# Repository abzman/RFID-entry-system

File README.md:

RFID-entry-system
=================

RFID entry system for i3 Detroit based on the Open Access Control 3.0, ethernet shield v5, arduino mega 2560, and Static Controls Corporation 1080 displays (RS485)

For an up to date overview please visit http://i3detroit.com/wi/index.php?title=RFID_entry_system

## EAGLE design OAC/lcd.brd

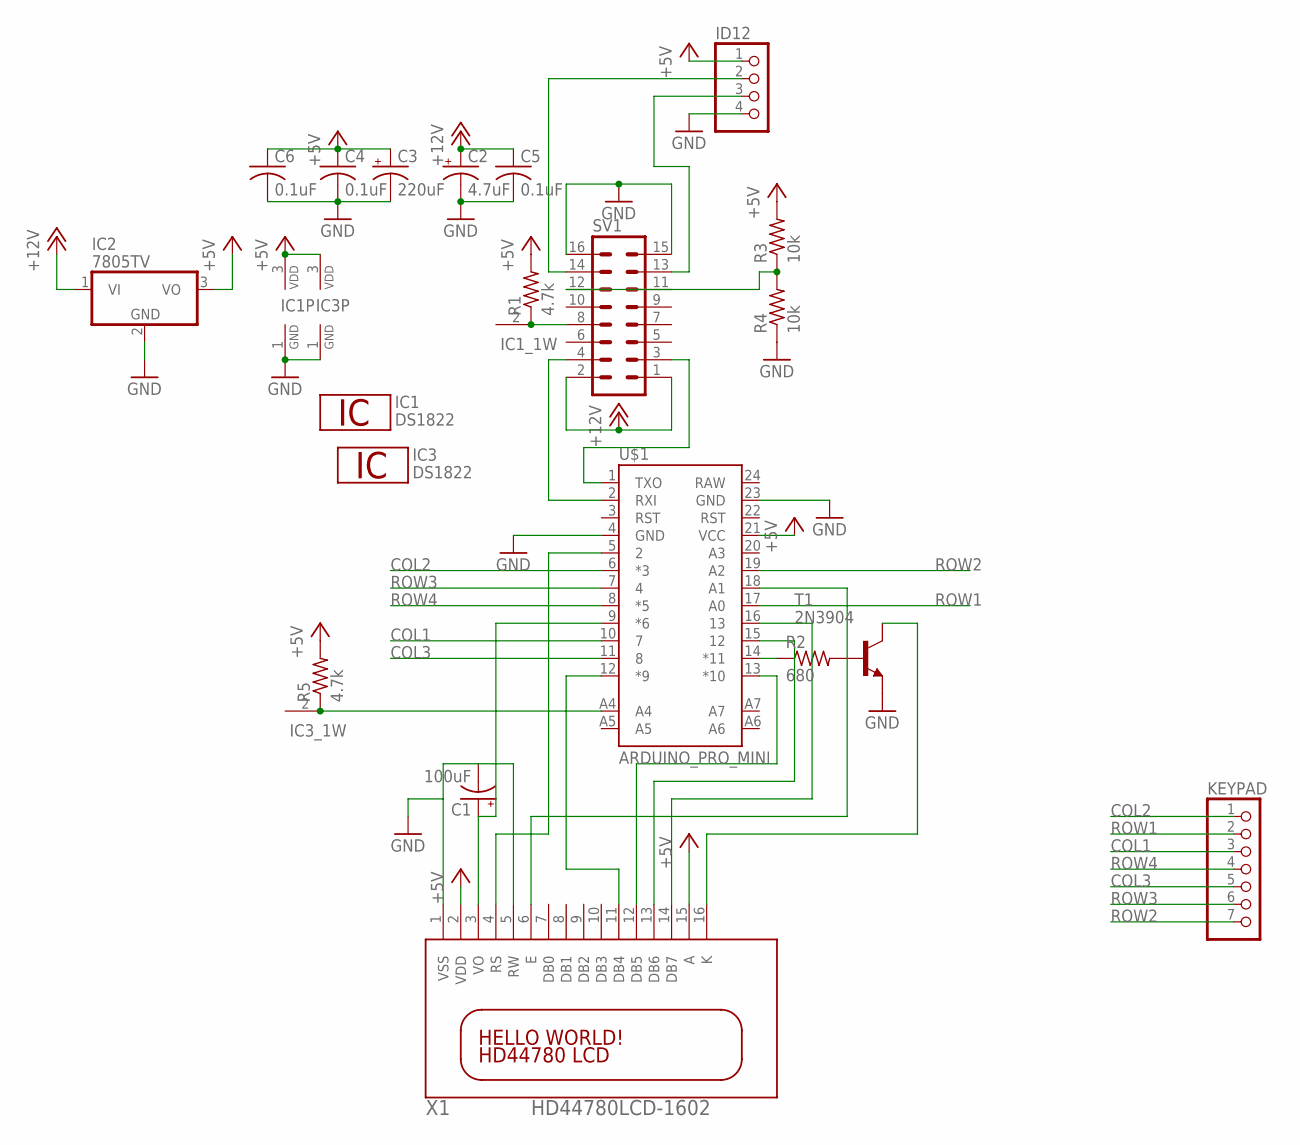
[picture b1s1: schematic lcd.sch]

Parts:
C1: 100uF; E2,5-7
C2: 4.7uF; E2,5-6
C3: 220uF; E5-8,5
C4, C5, C6: 0.1uF; C025-025X050
IC1, IC3: DS1822; TO92-
IC2: 7805TV; TO220V
ID12: PINHD-1X4; 1X04
KEYPAD: PINHD-1X7; 1X07
R1, R5: 4.7k; 0207/5V
R2: 680; 0207/5V
R3, R4: 10k; 0204V
SV1: ML16
T1: 2N3904; TO92
U$1: ARDUINO_PRO_MINI
X1: HD44780LCD-1602; LCD1602

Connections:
+5V: C3.+, C4.1, C6.1, IC1.3 (VDD), IC2.3 (VO), IC3.3 (VDD), ID12.1, R1.2, R3.2, R5.2, U$1.21 (VCC), X1.2 (VDD), X1.15 (A)
+12V: C2.+, C5.1, IC2.1 (VI), SV1.1, SV1.2
COL1: KEYPAD.3, U$1.10 (7)
COL2: KEYPAD.1, U$1.6 (*3)
COL3: KEYPAD.5, U$1.11 (8)
GND: C1.-, C2.-, C3.-, C4.2, C5.2, C6.2, IC1.1 (GND), IC2.2 (GND), IC3.1 (GND), ID12.4, R4.1, SV1.15, SV1.16, T1.3 (E), U$1.4 (GND), U$1.23 (GND), X1.1 (VSS), X1.5 (RW)
unnamed: IC1.2 (1W), R1.1, SV1.8
unnamed: C1.+, U$1.9 (*6), X1.3 (VO)
unnamed: SV1.4, U$1.2 (RXI)
unnamed: R2.1, U$1.14 (*11)
unnamed: R2.2, T1.2 (B)
unnamed: SV1.3, U$1.1 (TXO)
unnamed: ID12.2, SV1.14
unnamed: ID12.3, SV1.13
unnamed: T1.1 (C), X1.16 (K)
unnamed: U$1.5 (2), X1.4 (RS)
unnamed: U$1.18 (A1), X1.6 (E)
unnamed: U$1.12 (*9), X1.11 (DB4)
unnamed: U$1.13 (*10), X1.12 (DB5)
unnamed: U$1.15 (12), X1.13 (DB6)
unnamed: U$1.16 (13), X1.14 (DB7)
unnamed: R3.1, R4.2, SV1.12
unnamed: IC3.2 (1W), R5.1, U$1.A4
ROW1: KEYPAD.2, U$1.17 (A0)
ROW2: KEYPAD.7, U$1.19 (A2)
ROW3: KEYPAD.6, U$1.7 (4)
ROW4: KEYPAD.4, U$1.8 (*5)

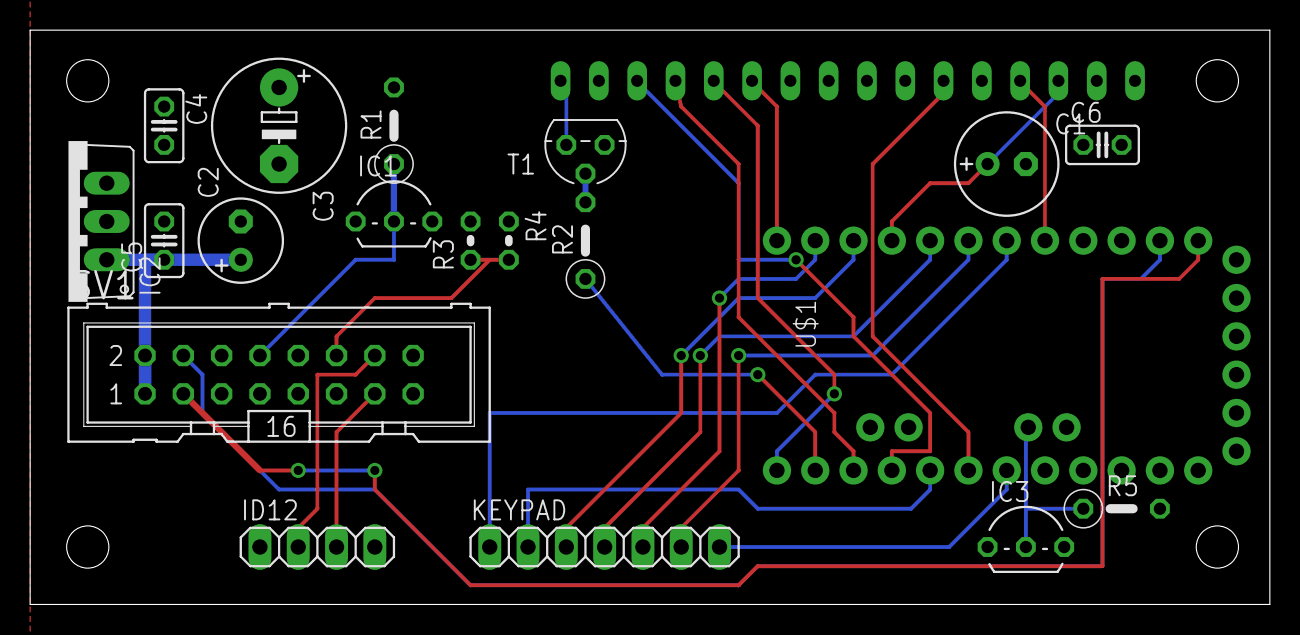
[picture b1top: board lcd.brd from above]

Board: 2 copper layers, 82.2 x 38.1 mm, 20 parts (1 on the bottom side), 27 nets.

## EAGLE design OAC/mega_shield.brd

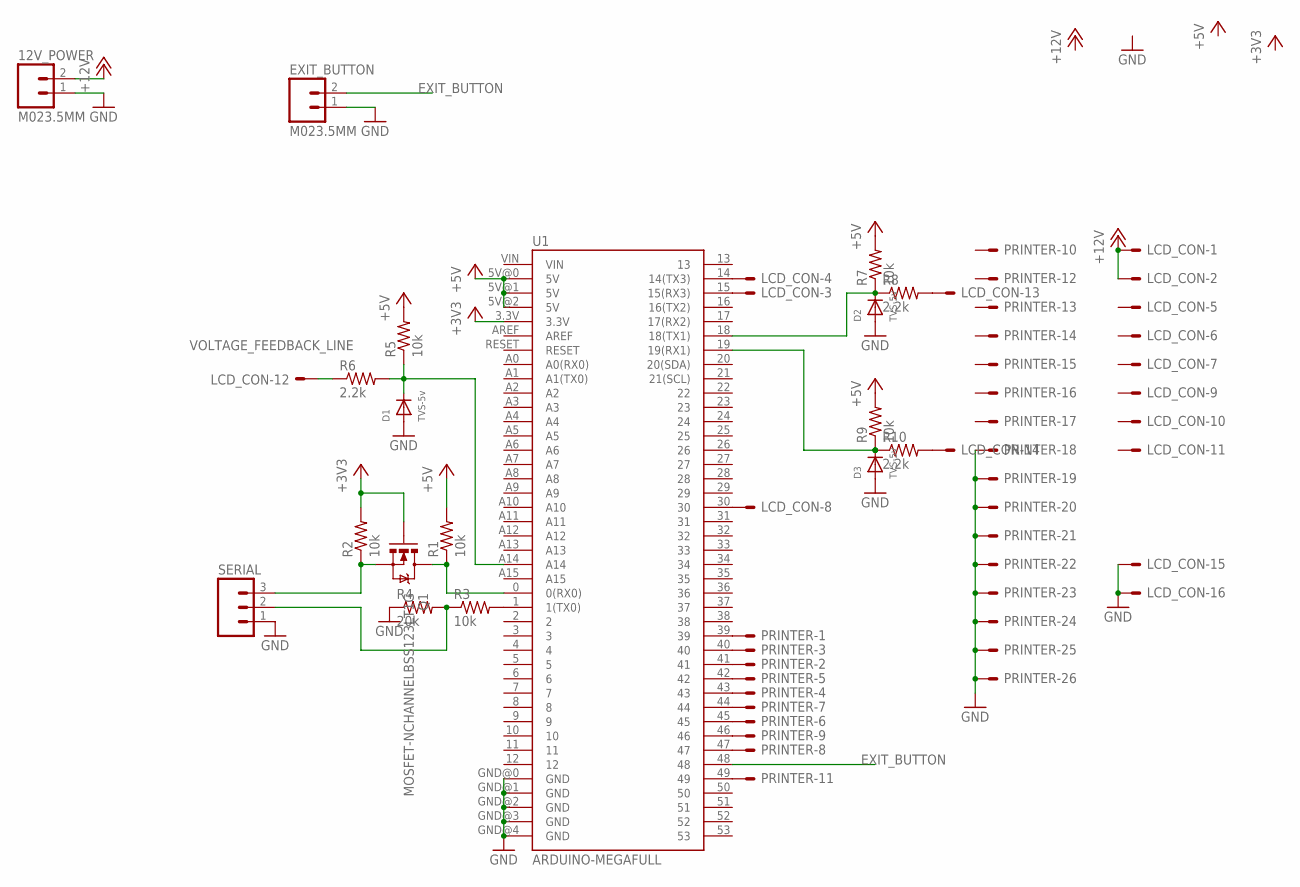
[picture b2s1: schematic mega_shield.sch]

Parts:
12V_POWER: M023.5MM; SCREWTERMINAL-3.5MM-2
D1, D2, D3: TVS-5v; SOD-123
EXIT_BUTTON: M023.5MM; SCREWTERMINAL-3.5MM-2
LCD_CON: ML16E; ML16
PRINTER: ML26E; ML26
Q1: MOSFET-NCHANNELBSS123LT1G; SOT23
R1, R2, R3, R5, R7, R9: 10k; R0603
R4: 20k; R0603
R6, R8, R10: 2.2k; R0603
SERIAL: M03SCREW; SCREWTERMINAL-3.5MM-3
U1: ARDUINO-MEGAFULL; ARDUINO_MEGA

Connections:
+3V3: Q1.1 (G), R2.2, U1.3.3V
+5V: R1.2, R5.2, R7.2, R9.2, U1.5V@0 (5V), U1.5V@1 (5V), U1.5V@2 (5V)
+12V: 12V_POWER.2, LCD_CON.1, LCD_CON.2
EXIT_BUTTON: EXIT_BUTTON.2, U1.48
GND: 12V_POWER.1, D1.A, D2.A, D3.A, EXIT_BUTTON.1, LCD_CON.15, LCD_CON.16, PRINTER.18, PRINTER.19, PRINTER.20, PRINTER.21, PRINTER.22, PRINTER.23, PRINTER.24, PRINTER.25, PRINTER.26, R4.1, SERIAL.1, U1.GND@0 (GND), U1.GND@1 (GND), U1.GND@2 (GND), U1.GND@3 (GND), U1.GND@4 (GND)
unnamed: LCD_CON.3, U1.15 (15(RX3))
unnamed: LCD_CON.4, U1.14 (14(TX3))
unnamed: PRINTER.1, U1.39
unnamed: PRINTER.11, U1.49
unnamed: PRINTER.2, U1.41
unnamed: PRINTER.3, U1.40
unnamed: PRINTER.4, U1.43
unnamed: PRINTER.5, U1.42
unnamed: PRINTER.6, U1.45
unnamed: PRINTER.7, U1.44
unnamed: PRINTER.8, U1.47
unnamed: PRINTER.9, U1.46
unnamed: LCD_CON.8, U1.30
unnamed: R3.2, U1.1 (1(TX0))
unnamed: R3.1, R4.2, SERIAL.2
unnamed: D1.C, R5.1, R6.2, U1.A14
unnamed: Q1.2 (S), R2.1, SERIAL.3
unnamed: Q1.3 (D), R1.1, U1.0 (0(RX0))
unnamed: D2.C, R7.1, R8.1, U1.18 (18(TX1))
unnamed: D3.C, R9.1, R10.1, U1.19 (19(RX1))
unnamed: LCD_CON.13, R8.2
unnamed: LCD_CON.14, R10.2
VOLTAGE_FEEDBACK_LINE: LCD_CON.12, R6.1

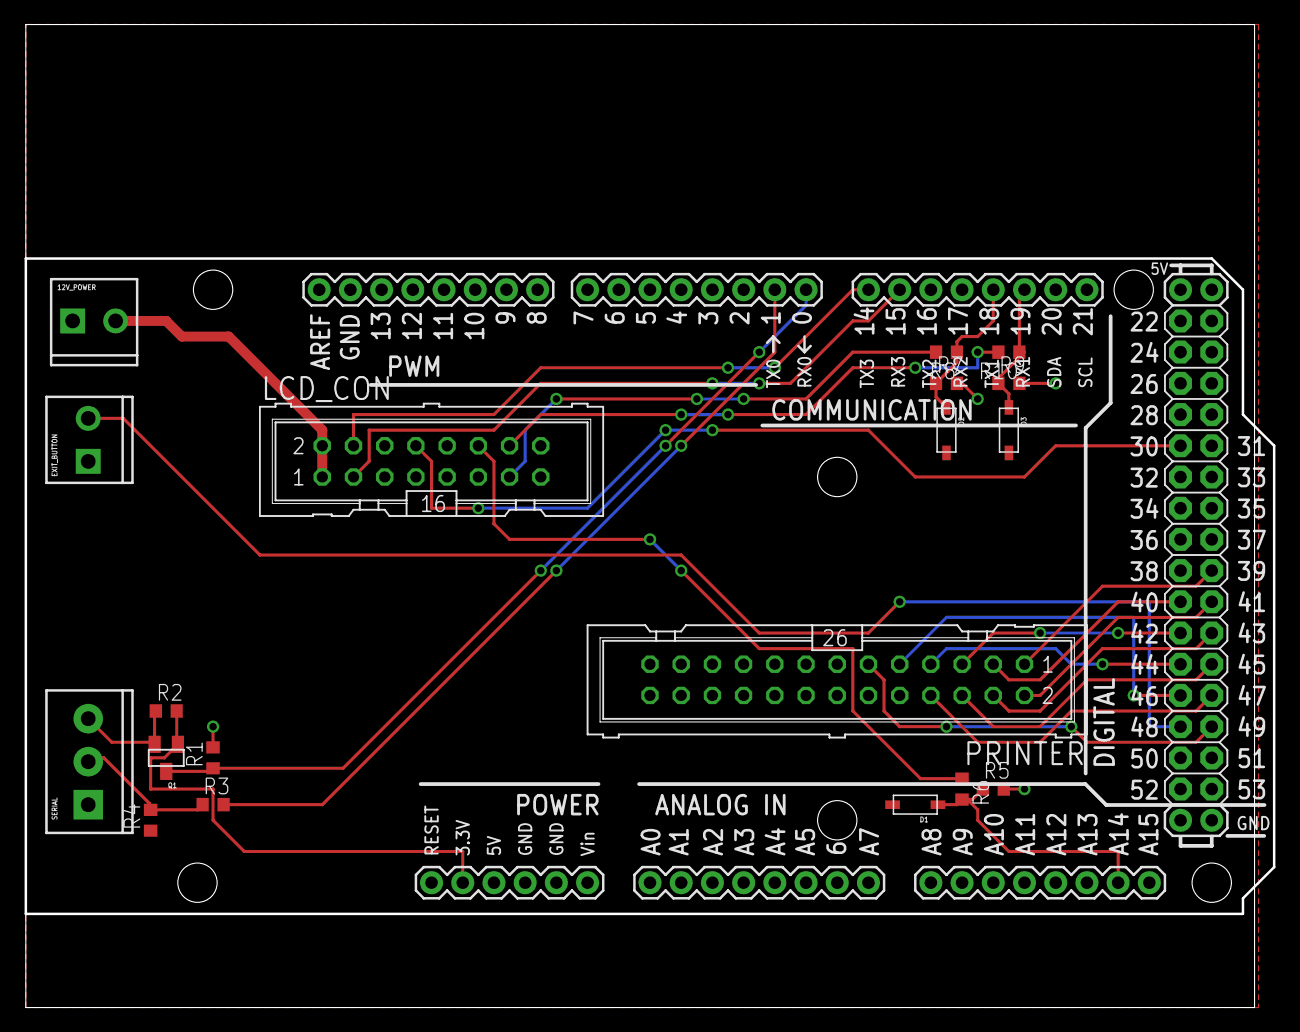
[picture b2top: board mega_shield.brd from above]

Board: 2 copper layers, 101.6 x 79.8 mm, 20 parts (0 on the bottom side), 28 nets.

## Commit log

2013-04-05 read working
2013-04-06 printer working
2013-06-19 everything working as a peripheral
2013-06-19 Everything working
2013-06-21 working everything (incliding printer)
2013-06-29 final commit before removing the SCC 1080 code (switching to HD44780)
2013-06-29 removedfiles not relevant to project, will create newrepo for the work on the SCC-1080s
2013-06-30 changed to 44780 on 3 wire 595 spi and a 4017 keypad matrix
2013-07-12 final configuration, still buggy
2013-07-13 contrast set command
2013-08-01 refactoring on paper, untested
2013-08-01 paper, second pass, still untested
2014-06-15 added uart_lcd
2014-06-15 added board files

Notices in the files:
parts and their libraries:
SparkFun-Boards: Licensing: CC v3.0 Share-Alike You are welcome to use this library for commercial purposes.
